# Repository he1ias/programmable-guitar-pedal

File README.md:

# programmable-guitar-pedal

A programmable acoustic guitar pedal that doubles as a wireless instrument recording device.

### What does it do?

This project allows you to test infinite different effects on your acoustic or electric without having to pay huge prices for expensive guitar pedals. Simply plug your guitar in as you would with any other guitar pedal, and access different effects and plugins via the built-in Raspberry Pi Pico's web interface.

### What's in this repo?

All the firmare & KiCad project files used to build this project!

You can access the KiCad project files [here](https://kicanvas.org/?repo=https://github.com/he1ias/programmable-guitar-pedal/blob/main/KiCad%20Files/).

### How was it built?

I started by making a prototype amplifier using breadboards & transistors:

I then developed the schematic using KiCad:

...and the PCB!

### How do I build it?

You can find the bill of materials in `bom.md` and `bom.csv`, I've also attached it below. KiCad project & gerber output files can also be found in this repository, as well as `.step` and `.stl` files ready to print the 3D guitar pedal case model.

| Item | Qty | Supplier | Cost/item | Total Cost | Link |
|------|----:|----------|----------:|-----------:|------|
| Potentiometers (w. Knobs) | 2 | LCSC | $0.57 | $1.14 | [Link](https://www.lcsc.com/product-detail/C470717.html) |
| Precision potentiometers | 5 | LCSC | $0.16 | $0.80 | [Link](https://www.lcsc.com/product-detail/C118945.html) |
| Op-amp | 5 | LCSC | $0.30 | $1.50 | [Link](https://www.lcsc.com/product-detail/C7377.html) |
| 1/4" guitar jacks | 2 | LCSC | $0.50 | $1.00 | [Link](https://www.lcsc.com/product-detail/C41409495.html) |
| JLCPCB | 1 | JLC | $10.00 | $10.00 | [Link](https://jlcpcb.com/) |
| Raspberry Pi Pico 2WH | 1 | Core electronics | $10.01 | $10.01 | [Link](https://core-electronics.com.au/raspberry-pi-pico-2-wh-with-headers.html) |
| DAC | 1 | Core electronics | $5.64 | $5.64 | [Link](https://core-electronics.com.au/adafruit-pcm5100-i2s-dac-line-level-output-100db-snr.html) |
| 20pin Female headers | 2 | Core electronics | $0.25 | $0.50 | [Link](https://core-electronics.com.au/0-100-2-54-mm-female-header-1x20-pin-straight.html) |
| 6.5mm male to 3mm female audio cable | 1 | Jaycar | $2.88 | $2.88 | [Link](https://www.jaycar.com.au/6-5mm-stereo-plug-to-3-5mm-stereo-socket-adaptor/p/PA3590) |
| Estimated total shipping | 1 | | | $14.00 | |

Total cost: ~$46.47 (USD).

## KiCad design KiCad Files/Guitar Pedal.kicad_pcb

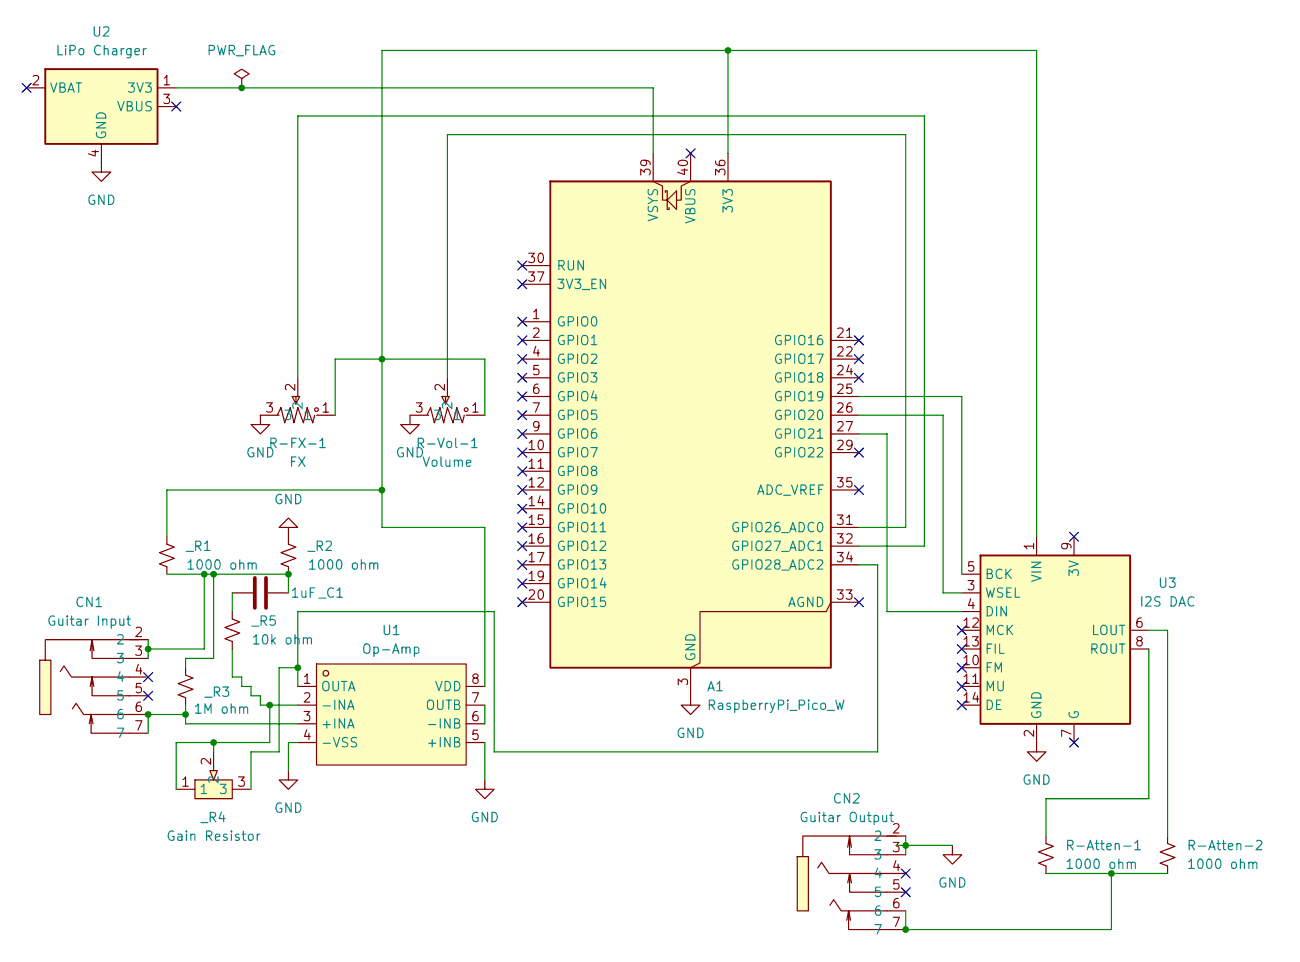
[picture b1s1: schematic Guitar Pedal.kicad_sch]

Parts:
A1: RaspberryPi_Pico_W; RPi_Pico2_WH_THT
CN1: Guitar Input; AUDIO-TH_PJ-611E; MPN PJ-611E; LCSC Part C41409495
CN2: Guitar Output; AUDIO-TH_PJ-611E; MPN PJ-611E; LCSC Part C41409495
R-Atten-1, R-Atten-2: 1000 ohm; R_Axial_DIN0207_L6.3mm_D2.5mm_P10.16mm_Horizontal
R-FX-1: FX; RES-ADJ-TH_RK09Y11L0001; MPN RK09Y11L0001; LCSC Part C470717
R-Vol-1: Volume; RES-ADJ-TH_RK09Y11L0001; MPN RK09Y11L0001; LCSC Part C470717
U1: Op-Amp; DIP-8_L9.4-W6.4-P2.54-LS9.1-BL; MPN MCP6002T-I/SN; LCSC Part C7377
U2: LiPo Charger; Makerverse_USB-C_LiPo_Charger_CE08374
U3: I2S DAC; Adafruit_PCM5100_I2S_DAC_ADA6251
_C1: 1uF; C_Disc_D5.0mm_W2.5mm_P2.50mm
_R1, _R2: 1000 ohm; R_Axial_DIN0207_L6.3mm_D2.5mm_P10.16mm_Horizontal
_R3: 1M ohm; R_Axial_DIN0207_L6.3mm_D2.5mm_P10.16mm_Horizontal
_R4: Gain Resistor; RES-ADJ-TH_3P-L7.1-W6.9-P2.50-L_3362P; MPN 3362P-1-105; LCSC Part C118945
_R5: 10k ohm; R_Axial_DIN0207_L6.3mm_D2.5mm_P10.16mm_Horizontal

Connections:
GND: A1.3 (GND), A1.8 (GND), A1.13 (GND), A1.18 (GND), A1.23 (GND), A1.28 (GND), A1.38 (GND), CN2.2, CN2.3, R-FX-1.3, R-Vol-1.3, U1.4 (-VSS), U1.5 (+INB), U2.4 (GND), U3.2 (GND), _R2.1
unnamed: A1.36 (3V3), R-FX-1.1, R-Vol-1.1, U1.8 (VDD), U3.1 (VIN), _R1.1
unnamed: A1.25 (GPIO19), U3.5 (BCK)
unnamed: A1.26 (GPIO20), U3.3 (WSEL)
unnamed: A1.27 (GPIO21), U3.4 (DIN)
unnamed: A1.31 (GPIO26_ADC0), R-Vol-1.2
unnamed: A1.32 (GPIO27_ADC1), R-FX-1.2
unnamed: A1.34 (GPIO28_ADC2), U1.1 (OUTA), _R4.3
unnamed: A1.39 (VSYS), U2.1 (3V3)
unnamed: CN1.2, CN1.3, _C1.2, _R1.2, _R2.2, _R3.1
unnamed: CN2.6, CN2.7, R-Atten-1.2, R-Atten-2.2
unnamed: CN1.6, CN1.7, U1.3 (+INA), _R3.2
unnamed: U1.2 (-INA), _R4.1, _R4.2, _R5.2
unnamed: U1.6 (-INB), U1.7 (OUTB)
unnamed: R-Atten-2.1, U3.6 (LOUT)
unnamed: R-Atten-1.1, U3.8 (ROUT)
unnamed: _C1.1, _R5.1

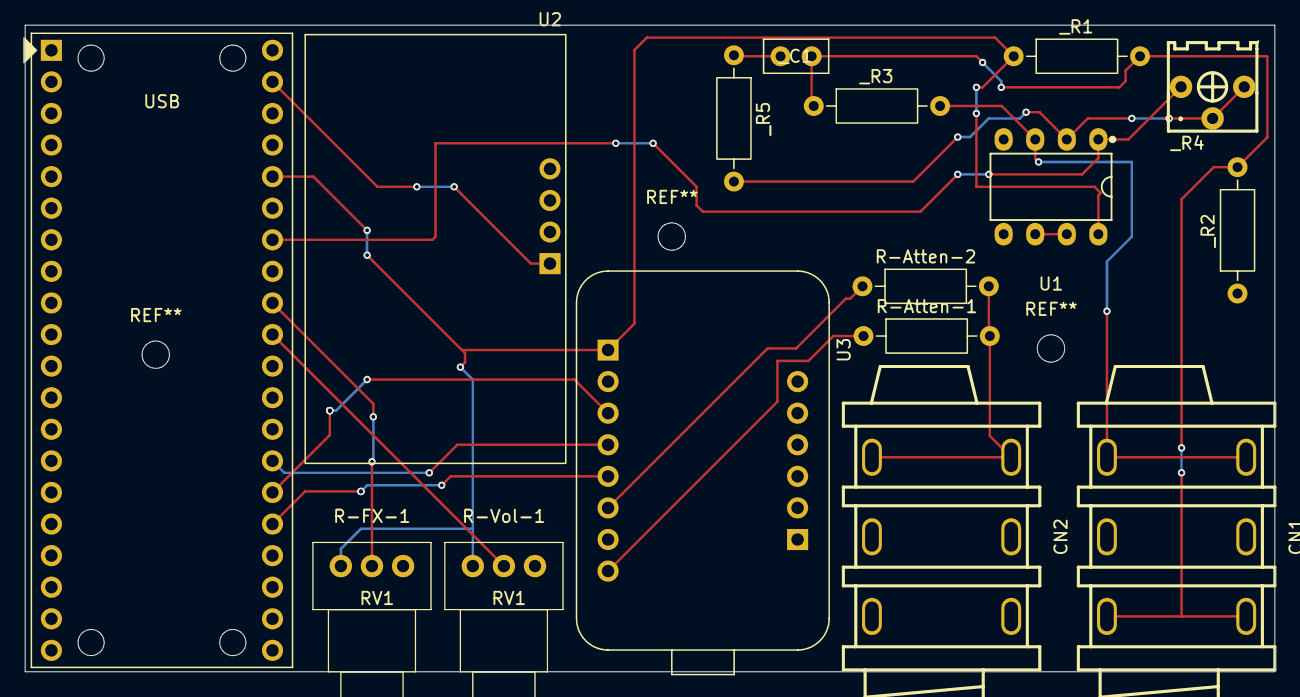
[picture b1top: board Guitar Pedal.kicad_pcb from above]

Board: 2 copper layers, 100.5 x 52.0 mm, 16 parts (0 on the bottom side), 17 nets.
